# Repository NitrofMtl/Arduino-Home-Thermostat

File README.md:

# OBSELETE

# Arduino-Home-Thermostat Version 2.2
10 rooms thermostat

Sketch for Arduino DUE that use 10 analogs inputs to read temperature and 10 digitals outputs to control solid state relay (SSR) on heater.

User can control options through GUI web page with ethernet shield.

User can name room and control setpoints for each channels. 
It also have an program page for schedule temperature for each rooms.
Program haves 4 mode of operation:
Single day (sunday to saturday).
Week day (monday to friday).
Week-end.
All day.

Web page is store on SD card.

Configurations, setpoints and program alarms are store on SD card and restore when arduino reboot.

Version 2.0 upgrades:
Upgraded library perfomance for analong reading.
Adding analog sequencer.
Upgraded weeklyAlarm library.
Added library to handle timning event interval so save mcu operation.
Rap most of webpage file inside index.htm to have less request and faster load of graphical user interface.
Upgraded rest interface.
General sketch structure upgrade, bugs fix...

# When upgrading to weeklyAlarm librarie 4.0.2, you should delete backup file in your sd card to reset configuration.

Check "Library-dependency-list.md" for all link of out side code.

  Copyright (c) 03/03/2017

    By Nitrof

  Permission is hereby granted, free of charge, to any person obtaining a copy of
  this software and associated documentation files (the "Software"), to deal in
  the Software without restriction, including without limitation the rights to
  use, copy, modify, merge, publish, distribute, sublicense, and/or sell copies of
  the Software, and to permit persons to whom the Software is furnished to do so,
  subject to the following conditions:

  The above copyright notice and this permission notice shall be included in all
  copies or substantial portions of the Software.

  THE SOFTWARE IS PROVIDED "AS IS", WITHOUT WARRANTY OF ANY KIND, EXPRESS OR
  IMPLIED, INCLUDING BUT NOT LIMITED TO THE WARRANTIES OF MERCHANTABILITY, FITNESS
  FOR A PARTICULAR PURPOSE AND NONINFRINGEMENT. IN NO EVENT SHALL THE AUTHORS OR
  COPYRIGHT HOLDERS BE LIABLE FOR ANY CLAIM, DAMAGES OR OTHER LIABILITY, WHETHER
  IN AN ACTION OF CONTRACT, TORT OR OTHERWISE, ARISING FROM, OUT OF OR IN
  CONNECTION WITH THE SOFTWARE OR THE USE OR OTHER DEALINGS IN THE SOFTWARE.

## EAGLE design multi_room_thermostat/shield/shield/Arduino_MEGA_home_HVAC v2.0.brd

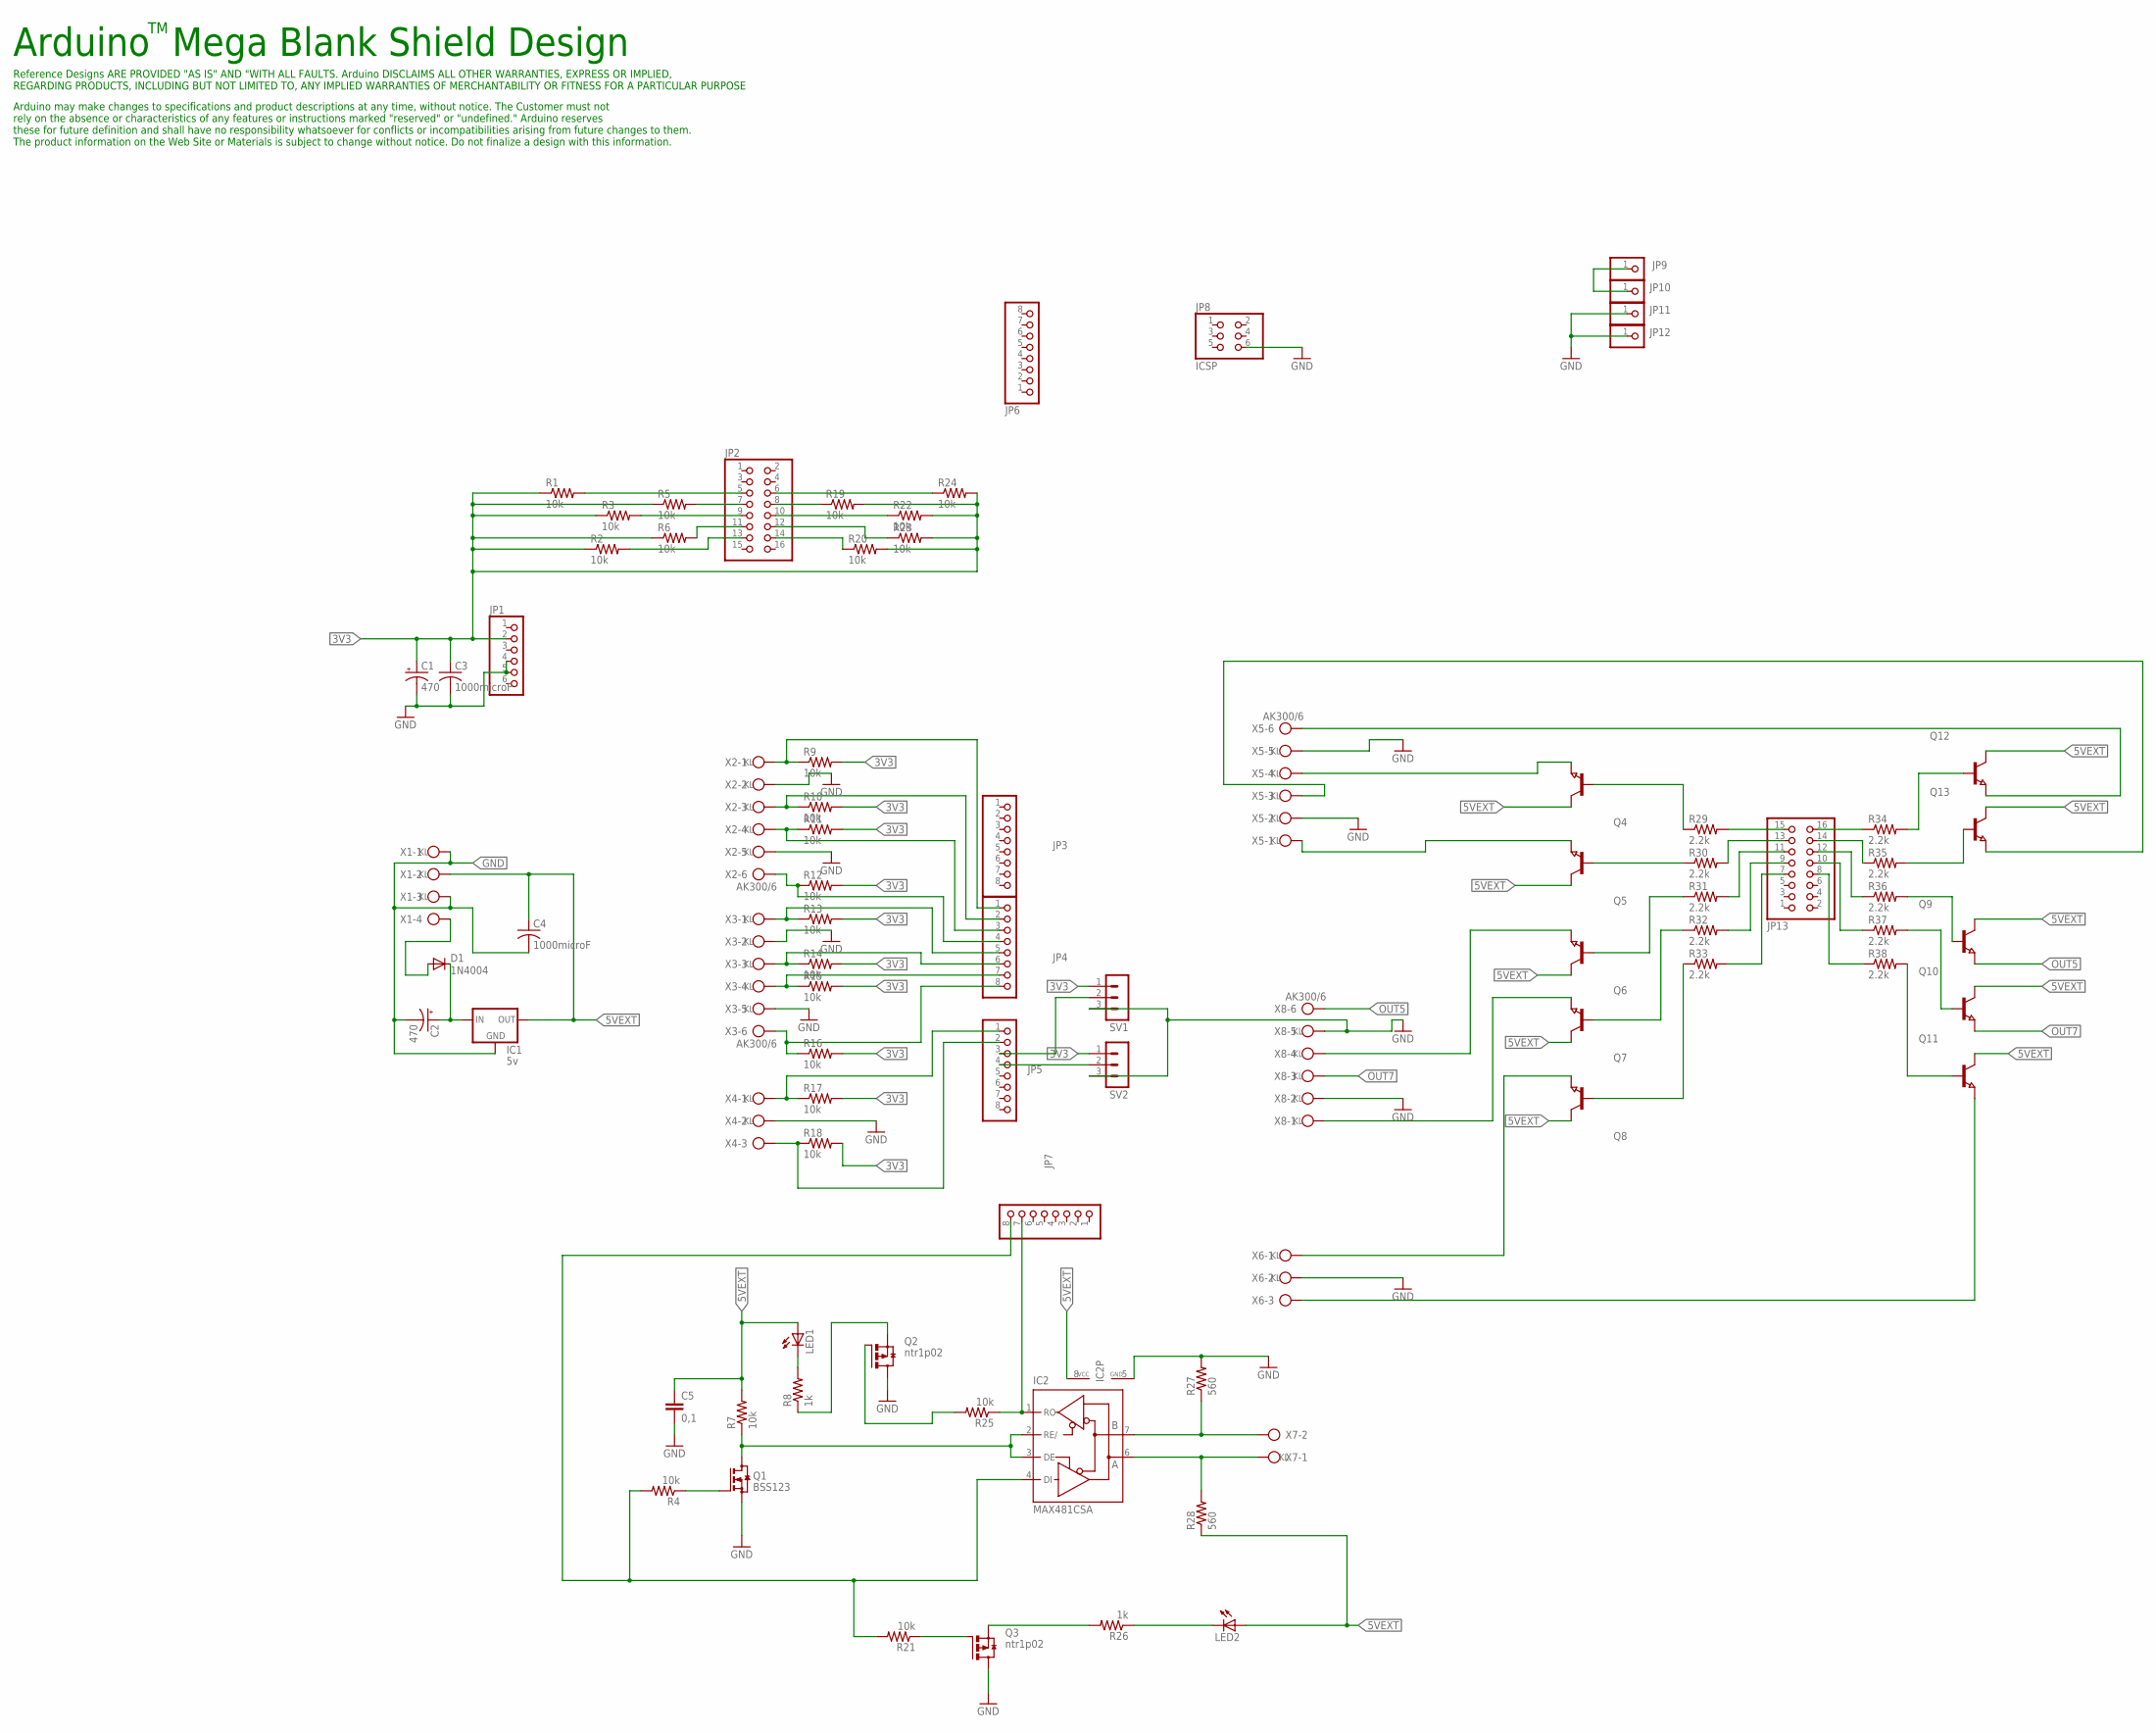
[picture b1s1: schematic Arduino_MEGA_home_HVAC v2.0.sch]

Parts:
C1, C2: 470; E5-6
C3, C4: 1000microF; C025-040X050
C5: 0,1; C2.5-2
D1: 1N4004; DO41-10
IC1: 5v; 78MXXL
IC2: MAX481CSA; SO08
JP1: PINHD-1X6; 1X06
JP2, JP13: PINHD-2X8; 2X08
JP3, JP4, JP5, JP6, JP7: PINHD-1X8; 1X08
JP8: ICSP; 2X03
JP9, JP10, JP11, JP12: PINHD-1X1; 1X01
LED1, LED2: LED_E; LED_1206
Q1: BSS123; SOT23
Q2, Q3: ntr1p02; SUPER-SOT3
Q4, Q5, Q6, Q7, Q8, Q9, Q10, Q11, Q12, Q13: NPN-TRANSISTOR_SOT23; SOT23
R1, R2, R3, R4, R5, R6, R7, R9, R10, R11, R12, R13, R14, R15, R16, R17, R18, R19, R20, R21, R22, R23, R24, R25: 10k; R0805
R8, R26: 1k; R0805
R27, R28: 560; R0805
R29, R30, R31, R32, R33, R34, R35, R36, R37, R38: 2.2k; M0805
SV1, SV2: MA03-1
X1: AK500/4
X2, X3, X5, X8: AK300/6
X4, X6: AK300/3
X7: AK300/2

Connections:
3V3: C1.+, C3.1, JP1.2, R1.1, R2.1, R3.1, R5.1, R6.1, R9.2, R10.2, R11.2, R12.2, R13.2, R14.2, R15.2, R16.2, R17.2, R18.2, R19.2, R20.2, R22.2, R23.2, R24.2, SV1.1, SV2.1
5VEXT: C4.1, C5.1, IC1.OUT, IC2.8 (VCC), LED1.A, LED2.A, Q4.3 (C), Q5.3 (C), Q6.3 (C), Q7.3 (C), Q8.3 (C), Q9.3 (C), Q10.3 (C), Q11.3 (C), Q12.3 (C), Q13.3 (C), R7.2, R28.1, X1.2
COM3RX: IC2.1 (RO), JP7.7, R25.1
COM3TX: IC2.4 (DI), JP7.8, R4.2, R21.2
GND: C1.-, C2.-, C3.2, C4.2, C5.2, IC1.GND, IC2.5 (GND), JP1.4, JP1.5, JP8.6, JP11.1, JP12.1, Q1.2 (S), Q2.3 (D), Q3.3 (D), R27.2, SV1.3, SV2.3, X1.1, X1.3, X2.2, X2.5, X3.2, X3.5, X4.2, X5.2, X5.5, X6.2, X8.2, X8.5
unnamed: JP4.8, R16.1, X3.6
unnamed: JP4.7, R15.1, X3.4
unnamed: JP4.6, R14.1, X3.3
unnamed: JP4.5, R13.1, X3.1
unnamed: JP4.1, R9.1, X2.1
unnamed: JP5.1, R17.1, X4.1
unnamed: JP4.3, R11.1, X2.4
unnamed: JP4.4, R12.1, X2.6
unnamed: JP5.2, R18.1, X4.3
unnamed: JP4.2, R10.1, X2.3
unnamed: JP13.15, R29.2
unnamed: JP13.16, R34.1
unnamed: JP13.14, R35.1
unnamed: JP13.12, R36.1
unnamed: JP13.10, R37.1
unnamed: JP13.13, R30.2
unnamed: JP13.11, R31.2
unnamed: JP13.9, R32.2
unnamed: JP13.8, R38.1
unnamed: JP13.7, R33.2
unnamed: Q4.1 (B), R29.1
unnamed: Q12.1 (B), R34.2
unnamed: Q5.1 (B), R30.1
unnamed: Q13.1 (B), R35.2
unnamed: Q4.2 (E), X5.4
unnamed: Q5.2 (E), X5.1
unnamed: Q13.2 (E), X5.3
unnamed: Q6.1 (B), R31.1
unnamed: Q6.2 (E), X8.4
unnamed: Q9.1 (B), R36.2
unnamed: Q7.1 (B), R32.1
unnamed: Q10.1 (B), R37.2
unnamed: Q8.2 (E), X6.1
unnamed: Q11.2 (E), X6.3
unnamed: Q7.2 (E), X8.1
unnamed: JP9.1, JP10.1
unnamed: Q11.1 (B), R38.2
unnamed: Q8.1 (B), R33.1
unnamed: Q12.2 (E), X5.6
unnamed: JP2.12, R23.1
unnamed: D1.A, X1.4
unnamed: C2.+, D1.C, IC1.IN
unnamed: JP5.3, SV1.2
unnamed: JP5.4, SV2.2
unnamed: IC2.2 (RE/), IC2.3 (DE), Q1.3 (D), R7.1
unnamed: LED1.C, R8.2
unnamed: Q1.1 (G), R4.1
unnamed: Q2.2 (S), R8.1
unnamed: JP2.14, R20.1
unnamed: JP2.11, R6.2
unnamed: JP2.13, R2.2
unnamed: IC2.7 (B), R27.1, X7.2
unnamed: JP2.6, R24.1
unnamed: JP2.5, R1.2
unnamed: JP2.7, R5.2
unnamed: JP2.8, R19.1
unnamed: JP2.10, R22.1
unnamed: JP2.9, R3.2
unnamed: IC2.6 (A), R28.2, X7.1
unnamed: Q2.1 (G), R25.2
unnamed: Q3.1 (G), R21.1
unnamed: Q3.2 (S), R26.2
unnamed: LED2.C, R26.1
OUT5: Q9.2 (E), X8.6
OUT7: Q10.2 (E), X8.3

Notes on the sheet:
Arduino Mega Blank Shield Design
Arduino may make changes to specifications and product descriptions at any time, without notice. The Customer must not rely on the absence or characteristics of any features or instructions marked "reserved" or "undefined." Arduino reserves these for future definition and shall have no responsibili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
Reference Designs ARE PROVIDED "AS IS" AND "WITH ALL FAULTS. Arduino DISCLAIMS ALL OTHER WARRANTIES, EXPRESS OR IMPLIED, REGARDING PRODUCTS, INCLUDING BUT NOT LIMITED TO, ANY IMPLIED WARRANTIES OF MERCHANTABILITY OR FITNESS FOR A PARTICULAR PURPOSE

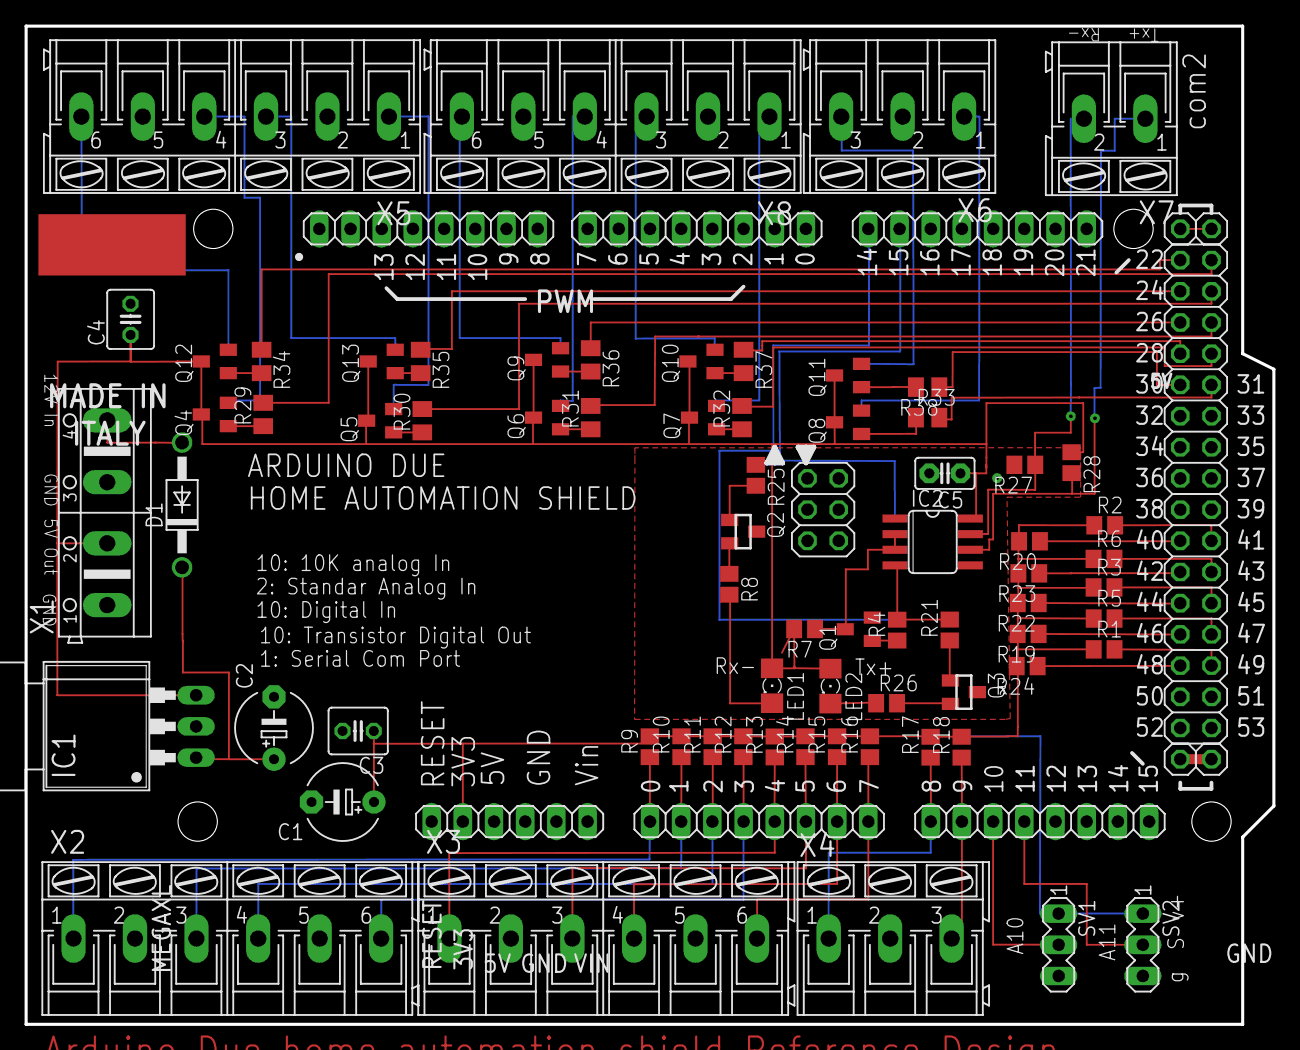
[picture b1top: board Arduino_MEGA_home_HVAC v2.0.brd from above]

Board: 2 copper layers, 101.6 x 81.3 mm, 84 parts (0 on the bottom side), 70 nets.

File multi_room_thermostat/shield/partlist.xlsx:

part | quantity | mouser ID | unity price | package size | package price | package size | package price |  | total price | arduino due homeautomation shield and extension
resistor |  |  |  |  |  |  |  |  |  | http://www.mouser.com/ProjectManager/ProjectDetail.aspx?Acce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
10k | 22 | 667-ERJ-P6WF1002V | 0.98899999999999999 | 10 | 0.41399999999999998 | 100 | 0.23 |  | 12.42 | d68a51ec02
2.2k | 10 | 667-ERA-6AEB222V | 0.76 | 10 | 0.30099999999999999 |  |  |  | 3.01
1k | 2 | 667-ERJ-P6WF1001V | 0.98899999999999999 | 10 | 0.41399999999999998 |  |  |  | 1.978
560Ω | 2 | 667-ERJ-P6WF5600V | 0.98899999999999999 | 10 | 0.41399999999999998 |  |  |  | 1.978
120Ω TROUGH HOLE | 1 | 279-CFR16J120R | 0.121 |  |  |  |  |  | 0.121
capacitor
electrolytic 470µF | 2 | 647-UPW2A471MHD | 1.81 |  |  |  |  |  | 3.62
ceramic 0,1µF | 1 | GRM2165C1H101JA01D | 0.14499999999999999 |  |  |  |  |  | 0.14499999999999999
electrolytic 1000µF | 2 | 581-TAJR104K035RNJ | 0.88 |  |  |  |  |  | 1.76
diode
1n4004 | 1 | 512-1N4004 | 0.16900000000000001 |  |  |  |  |  | 0.16900000000000001
led
 | 2 | 749-SM1206NPGC-IL | 1.33 |  |  |  |  |  | 2.66
transistor
SST2222A | 10 | 755-SST2222AT116 | 0.41 | 10 | 0.27100000000000002 |  |  |  | 2.71
mosfet
bss123 | 1 | 512-BSS123 | 0.28899999999999998 |  |  |  |  |  | 0.28899999999999998
ntr1p02 | 2 | 863-NTR1P02T1G | 0.56699999999999995 | 10 | 0.32800000000000001 |  |  |  | 1.1339999999999999
chip
v-reg lm7805 | 1 | 512-LM7805ACT | 0.83199999999999996 |  |  |  |  |  | 0.83199999999999996
MAX481CSA (rs485) | 1 | 700-MAX481CSA | 2.36 |  |  |  |  |  | 2.36
arduino header
1x6 | 1
1x8 (2pack) | 4.5 | 782-A000085 | 1.34 | 10 | 1.25 |  |  |  | 6.7
1x10(2pack) | 3 | 782-A000086 | 1.34 | 10 | 1.25 |  |  |  | 3.1339999999999999
2x18 | 1
2x3 | 1
screw header
ak500/6 | 6 | 845-30.706 | 2.93 | 10 | 2.1800000000000002 |  |  |  | 17.579999999999998
ak500/3 | 2 | 845-30.703 | 1.64 | 10 | 1.17 |  |  |  | 3.28
ak500/2 | 2 | 845-30.702 | 1.21 |  |  |  |  |  | 2.42
ak500/4 | 1 | 845-30.704 | 2.17 |  |  |  |  |  | 2.17
ak500/9 | 3 | 845-30.709 | 3.48 | 10 | 2.44 |  |  |  | 10.44
pin headers | 1 | 571-2-826925-0 | 2.44 |  |  |  |  |  | 2.44
connector
???3pin | 2
 |  |  |  |  |  |  | total |  | 83.350000000000009

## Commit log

2016-04-06 Added files via upload
2017-03-01 edit readme for 2.0
2017-03-02 Version 2.0
2017-03-02 format readme
2017-03-03 added muted comment dor internet shield1
2017-03-04 updating sd web page files
2018-02-18 fix decimal point rounding
2018-02-18 add delay to net setup
2018-03-30 add 'unchange' param to setpoint schedule
2018-04-02 fix json NaN parsing
2018-04-15 update IOCtrl
2018-04-21 match uhttp update
2018-05-27 add websocket server
2018-06-17 some progress on websocket
2018-07-19 add websocket configInputs
2018-07-22 finish WS server service
2018-07-22 fix name subscription typos
2018-08-02 adding new ionic app2.0
2018-08-03 remove app folder and link repos
2018-08-04 add ntp getbyhostname
2018-08-05 new NTPgetTime + time online tracking
2018-08-05 add arduino online time in app
2018-08-16 debuggin UWP
2018-08-17 add windows platform
2018-08-19 add loadpage
2018-09-16 update dependency list
2018-09-29 upgrading weekly alarm to 4.0.2
2018-09-30 update app + new IOctrl + debug weekly alarm
2018-12-17 v2.1 fix home onoff
2018-12-19 add fixed point to home
2018-12-30 add heating stage icon
2020-03-04 v2.2
2022-06-02 Bump @angular/core from 5.2.11 to 11.0.5 in /app/src/ardThermostatApp
    Bumps [@angular/core](https://github.com/angular/angular/tree/HEAD/packages/core) from 5.2.11 to 11.0.5.
    - [Release notes](https://github.com/angular/angular/releases)
    - [Changelog](https://github.com/angular/angular/blob/main/CHANGELOG.md)
    - [Commits](https://github.com/angular/angular/commits/11.0.5/packages/core)
    ---
    updated-dependencies:
2022-11-09 Bump loader-utils from 1.1.0 to 1.4.1 in /app/src/ardThermostatApp
    Bumps [loader-utils](https://github.com/webpack/loader-utils) from 1.1.0 to 1.4.1.
    - [Release notes](https://github.com/webpack/loader-utils/releases)
    - [Changelog](https://github.com/webpack/loader-utils/blob/v1.4.1/CHANGELOG.md)
    - [Commits](https://github.com/webpack/loader-utils/compare/v1.1.0...v1.4.1)
    ---
    updated-dependencies:
2022-11-13 Bump json-schema and jsprim in /app/src/ardThermostatApp
    Bumps [json-schema](https://github.com/kriszyp/json-schema) and [jsprim](https://github.com/joyent/node-jsprim). These dependencies needed to be updated together.
    Updates `json-schema` from 0.2.3 to 0.4.0
    - [Release notes](https://github.com/kriszyp/json-schema/releases)
    - [Commits](https://github.com/kriszyp/json-schema/compare/v0.2.3...v0.4.0)
    Updates `jsprim` from 1.4.1 to 1.4.2
    - [Release notes](https://github.com/joyent/node-jsprim/releases)
2022-11-13 Bump plist, cordova-android and cordova-windows
    Bumps [plist](https://github.com/TooTallNate/node-plist) to 3.0.6 and updates ancestor dependencies [plist](https://github.com/TooTallNate/node-plist), [cordova-android](https://github.com/apache/cor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
    Updates `plist` from 3.0.1 to 3.0.6
    - [Release notes](https://github.com/TooTallNate/node-plist/releases)
    - [Changelog](https://github.com/TooTallNate/plist.js/blob/master/History.md)
    - [Commits](https://github.com/TooTallNate/node-plist/commits)
    Updates `cordova-android` from 7.1.4 to 11.0.0
2022-12-02 Bump decode-uri-component in /app/src/ardThermostatApp
    Bumps [decode-uri-component](https://github.com/SamVerschueren/decode-uri-component) from 0.2.0 to 0.2.2.
    - [Release notes](https://github.com/SamVerschueren/decode-uri-component/releases)
    - [Commits](https://github.com/SamVerschueren/decode-uri-component/compare/v0.2.0...v0.2.2)
    ---
    updated-dependencies:
    - dependency-name: decode-uri-component
2022-12-06 Bump qs and express in /app/src/ardThermostatApp
    Bumps [qs](https://github.com/ljharb/qs), [qs](https://github.com/ljharb/qs), [qs](https://github.com/ljharb/qs) and [express](https://github.com/expressjs/express). These dependencies needed to be u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
    Updates `qs` from 6.5.2 to 6.11.0
    - [Release notes](https://github.com/ljharb/qs/releases)
    - [Changelog](https://github.com/ljharb/qs/blob/main/CHANGELOG.md)
    - [Commits](https://github.com/ljharb/qs/compare/v6.5.2...v6.11.0)
    Updates `qs` from 6.3.2 to 6.11.0
2022-12-08 Bump express from 4.16.3 to 4.18.2 in /app/src/ardThermostatApp
    Bumps [express](https://github.com/expressjs/express) from 4.16.3 to 4.18.2.
    - [Release notes](https://github.com/expressjs/express/releases)
    - [Changelog](https://github.com/expressjs/express/blob/master/History.md)
    - [Commits](https://github.com/expressjs/express/compare/4.16.3...4.18.2)
    ---
    updated-dependencies:
2023-02-28 Bump minimist and mkdirp in /app/src/ardThermostatApp
    Bumps [minimist](https://github.com/minimistjs/minimist) and [mkdirp](https://github.com/isaacs/node-mkdirp). These dependencies needed to be updated together.
    Updates `minimist` from 1.2.0 to 1.2.8
    - [Release notes](https://github.com/minimistjs/minimist/releases)
    - [Changelog](https://github.com/minimistjs/minimist/blob/main/CHANGELOG.md)
    - [Commits](https://github.com/minimistjs/minimist/compare/v1.2.0...v1.2.8)
    Updates `mkdirp` from 0.5.1 to 0.5.6
